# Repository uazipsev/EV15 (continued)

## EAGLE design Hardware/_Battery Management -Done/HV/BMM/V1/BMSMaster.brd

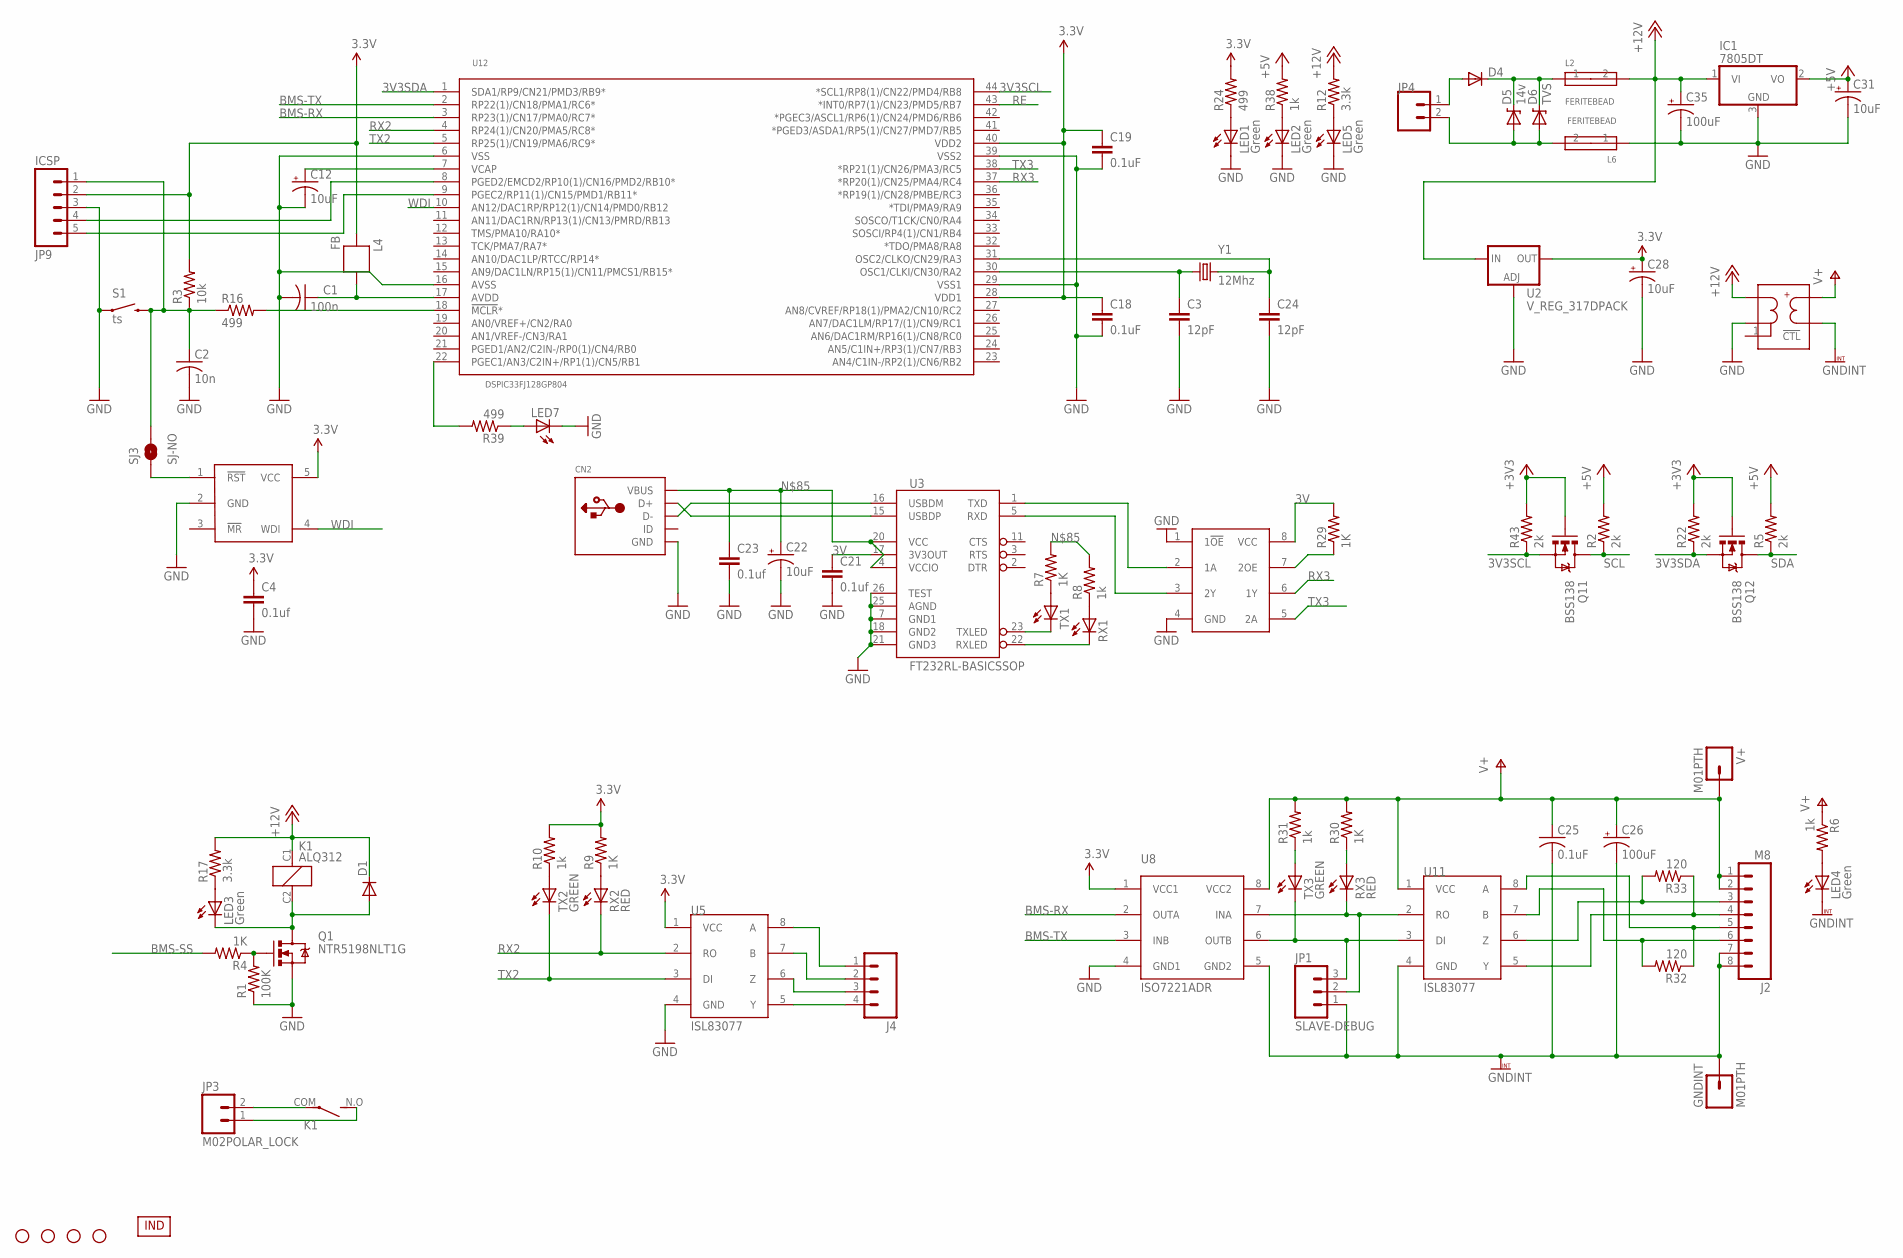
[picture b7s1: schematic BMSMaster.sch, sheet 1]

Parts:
C1: 100n; C0805
C2: 10n; C0805
C3, C24: 12pF; 0805
C4, C21, C23: 0.1uf; 0805
C12, C22, C31: 10uF; EIA3216
C18, C19: 0.1uF; 0805
C25: 0.1uF; C0805
C26: 100uF; C/6032-28W
C28: 10uF; POLC1206
C35: 100uF; CT7343
CN2: USBMOLEX; USB-MINIB-THM-MOLEX
D1: DIODESMB; SMB-DIODE
D4: DIODESMA; SMA-DIODE
D5: 14v; SMB-DIODE
D6: TVS; DO-214AC
GNDINT: M01PTH; 1X01
IC1: 7805DT; TO252
J2: M8; 75869-132LF
J4: M04POLAR_LOCK; MOLEX-1X4_LOCK
JP1: SLAVE-DEBUG; 1X03_LOCK_LONGPADS
JP3, JP4: M02POLAR_LOCK; MOLEX-1X2_LOCK
JP9: ICSP; 1X05_LOCK_LONGPADS
K1: ALQ312
L2, L6: FERITEBEAD; 0603
L4: FB; 0603
LED1, LED2, LED3, LED4, LED5: Green; CHIPLED_0805
LED7: LEDCHIP-LED0805; CHIP-LED0805
Q1: NTR5198NLT1G; SOT23
Q11, Q12: BSS138; SOT23-3
R1: 100K; R0805
R2, R5, R22, R43: 2k; R0805
R3: 10k; 0805
R4, R7, R9, R29, R30: 1K; R0805
R6, R8, R10, R31, R38: 1k; R0805
R12, R17: 3.3k; R0805
R16, R39: 499; 0805
R24: 499; R0805
R32, R33: 120; R0805
RX1: LEDCHIPLED_0805; CHIPLED_0805
RX2, RX3: RED; CHIPLED_0805
S1: ts; TACTILE-PTH-SIDEEZ
SJ3: SJ-NO; SJ_2S-NO
STANDOFF1, STANDOFF2, STANDOFF3, STANDOFF4: STAND-OFF
TX1: LEDCHIPLED_0805; CHIPLED_0805
TX2, TX3: GREEN; CHIPLED_0805
U2: V_REG_317DPACK; V-REG_DPACK
U3: FT232RL-BASICSSOP; SSOP28DB
U4: SN74LVC2G241DCTR; VFSOP-8
U5, U11: ISL83077; SO08
U8: ISO7221ADR; SOIC-8
U9: MAX823; SOT23-5L
U12: DSPIC33FJ128GP804; TQFP-44
U21: REC7.5-1205SRW/H2/A/M; 24DIPMOD-8LEAD
U$1: INDPK1; PICKIT-PIN-1
V+: M01PTH; 1X01
Y1: 12Mhz; CRYSTAL-SMD-5X3

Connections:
3.3V: C4.1, C18.1, C19.1, C28.1 (+), JP9.2, L4.2, R3.2, R9.2, R10.2, R24.2, U2.4 (OUT), U5.1 (VCC), U8.1 (VCC1), U9.5 (VCC), U12.28 (VDD1), U12.40 (VDD2)
3V: C21.1, R29.2, U3.17 (3V3OUT), U4.8 (VCC)
3V3SCL: Q11.2 (S), R43.1, U12.44 (*SCL1/RP8(1)/CN22/PMD4/RB8)
3V3SDA: Q12.2 (S), R22.1, U12.1 (SDA1/RP9/CN21/PMD3/RB9*)
+3V3: Q11.1 (G), Q12.1 (G), R22.2, R43.2
+5V: C31.A (+), IC1.2 (VO), R2.2, R5.2, R38.2; also elsewhere on the board
+12V: C35.+, D1.C, IC1.1 (VI), K1.C1 (+), L2.2, R12.2, R17.2, U2.3 (IN), U21.22 (VIN+), U21.23 (VIN+)
BMS-RX: U8.2 (OUTA), U12.3 (RP23(1)/CN17/PMA0/RC7*)
BMS-SS: R4.2
BMS-TX: U8.3 (INB), U12.2 (RP22(1)/CN18/PMA1/RC6*)
GND: C1.2, C2.2, C3.2, C4.2, C12.C (-), C18.2, C19.2, C21.2, C22.C (-), C23.2, C24.2, C28.2 (-), C31.C (-), C35.-, CN2.GND, IC1.3 (GND), JP9.3, L6.1, LED1.C, LED2.C, LED5.C, LED7.C, Q1.2 (S), R1.1, S1.1, U2.1 (ADJ), U3.7 (GND1), U3.18 (GND2), U3.21 (GND3), U3.25 (AGND), U3.26 (TEST), U4.1 (1!OE), U4.4 (GND), U5.4 (GND), U8.4 (GND1), U9.2 (GND), U12.6 (VSS), U12.16 (AVSS), U12.29 (VSS1), U12.39 (VSS2), U21.2 (VIN-), U21.3 (VIN-); also elsewhere on the board
GNDINT: C25.2, C26.-, GNDINT.1, J2.7, J2.8, JP1.1, LED4.C, U8.5 (GND2), U11.4 (GND), U21.16 (VOUT-)
unnamed: LED7.A, R39.1
unnamed: C24.1, U12.31 (OSC2/CLKO/CN29/RA3), Y1.3 (2)
unnamed: J4.4, U5.5 (Y)
unnamed: C3.1, U12.30 (OSC1/CLKI/CN30/RA2), Y1.1
unnamed: SJ3.1, U9.1 (!RST)
unnamed: CN2.D-, U3.16 (USBDM)
unnamed: LED1.A, R24.1
unnamed: CN2.D+, U3.15 (USBDP)
unnamed: LED5.A, R12.1
unnamed: R7.1, TX1.A
unnamed: J4.3, U5.6 (Z)
unnamed: J4.2, U5.7 (B)
unnamed: J4.1, U5.8 (A)
unnamed: R8.1, RX1.A
unnamed: TX1.C, U3.23 (TXLED)
unnamed: RX1.C, U3.22 (RXLED)
unnamed: R10.1, TX2.A
unnamed: U3.1 (TXD), U4.2 (1A)
unnamed: JP3.2, K1.COM
unnamed: U3.5 (RXD), U4.3 (2Y)
unnamed: C1.1, L4.1, U12.17 (AVDD)
unnamed: LED2.A, R38.1
unnamed: JP3.1, K1.N.O (S)
unnamed: J2.3, R33.2, U11.6 (Z)
unnamed: C12.A (+), U12.7 (VCAP)
unnamed: LED4.A, R6.2
unnamed: D1.A, K1.C2 (-), LED3.C, Q1.3 (D)
unnamed: Q1.1 (G), R1.2, R4.1
unnamed: R9.1, RX2.A
unnamed: J2.4, R33.1, U11.5 (Y)
unnamed: J2.5, R32.1, U11.8 (A)
unnamed: J2.6, R32.2, U11.7 (B)
unnamed: R39.2, U12.22 (PGEC1/AN3/C2IN+/RP1(1)/CN5/RB1)
unnamed: C2.1, JP9.1, R3.1, R16.1, S1.2, SJ3.2
unnamed: R16.2, U12.18 (!MCLR!*)
unnamed: JP9.4, U12.8 (PGED2/EMCD2/RP10(1)/CN16/PMD2/RB10*)
unnamed: JP9.5, U12.9 (PGEC2/RP11(1)/CN15/PMD1/RB11*)
unnamed: LED3.A, R17.1
unnamed: R29.1, U4.7 (2OE)
unnamed: R30.1, RX3.A
unnamed: R31.1, TX3.A
unnamed: C22.A (+), C23.1, CN2.VBUS, R7.2, R8.2, U3.4 (VCCIO), U3.20 (VCC)
unnamed: D5.A, D6.A, JP4.2, L6.2
unnamed: D4.A, JP4.1
unnamed: D4.C, D5.C, D6.C, L2.1
PIC1: JP1.2, RX3.C, U8.7 (INA), U11.2 (RO)
PIC2: JP1.3, TX3.C, U8.6 (OUTB), U11.3 (DI)
RE: U12.43 (*INT0/RP7(1)/CN23/PMD5/RB7)
RX2: RX2.C, U5.2 (RO), U12.4 (RP24(1)/CN20/PMA5/RC8*)
RX3: U4.6 (1Y), U12.37 (*RP20(1)/CN25/PMA4/RC4)
SCL: Q11.3 (D), R2.1; also elsewhere on the board
SDA: Q12.3 (D), R5.1; also elsewhere on the board
TX2: TX2.C, U5.3 (DI), U12.5 (RP25(1)/CN19/PMA6/RC9*)
TX3: U4.5 (2A), U12.38 (*RP21(1)/CN26/PMA3/RC5)
V+: C25.1, C26.+, J2.1, J2.2, R6.1, R30.2, R31.2, U8.8 (VCC2), U11.1 (VCC), U21.14 (VOUT+), V+.1
WDI: U9.4 (WDI), U12.10 (AN12/DAC1RP/RP12(1)/CN14/PMD0/RB12)

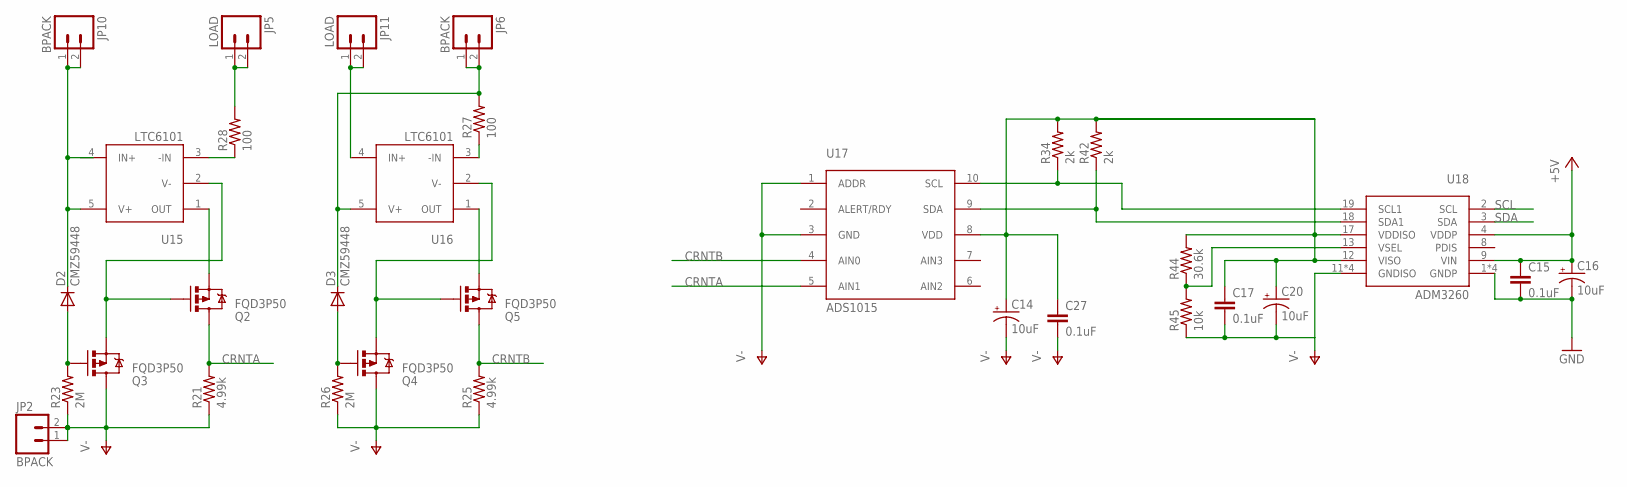
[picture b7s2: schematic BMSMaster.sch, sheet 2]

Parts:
C14, C16, C20: 10uF; EIA3216
C15, C17, C27: 0.1uF; 0805
D2, D3: CMZ59448; DIODE-HV
JP2, JP6, JP10: BPACK; MOLEX-1X2_LOCK
JP5, JP11: LOAD; MOLEX-1X2_LOCK
Q2, Q3, Q4, Q5: FQD3P50; DPAK
R21, R25: 4.99k; 1206
R23, R26: 2M; 1206
R27, R28: 100; 1206
R34, R42: 2k; 0805
R44: 30.6k; 0805
R45: 10k; 0805
U15, U16: LTC6101; SOT23-5
U17: ADS1015; MSOP-10
U18: ADM3260; SSOP-20

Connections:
+5V: C15.1, C16.A (+), U18.4 (VDDP), U18.9 (VIN); also elsewhere on the board
CRNTA: Q2.2 (D), R21.2, U17.5 (AIN1)
CRNTB: Q5.2 (D), R25.2, U17.4 (AIN0)
GND: C15.2, C16.C (-), U18.1 (GNDP), U18.5 (GNDP), U18.7 (GNDP), U18.10 (GNDP); also elsewhere on the board
unnamed: D3.C, JP6.1, JP6.2, R27.2, U16.5 (V+)
unnamed: JP5.1, JP5.2, R28.2
unnamed: D2.C, JP10.1, JP10.2, U15.4 (IN+), U15.5 (V+)
unnamed: D3.A, Q4.1 (G), R26.2
unnamed: C14.A (+), C17.1, C20.A (+), C27.1, R34.2, R42.2, R44.2, U17.8 (VDD), U18.12 (VISO), U18.17 (VDDISO)
unnamed: JP11.1, JP11.2, U16.4 (IN+)
unnamed: D2.A, Q3.1 (G), R23.2
unnamed: R34.1, U17.10 (SCL), U18.19 (SCL1)
unnamed: R27.1, U16.3 (-IN)
unnamed: Q2.1 (G), Q3.3 (S), U15.2 (V-)
unnamed: Q2.3 (S), U15.1 (OUT)
unnamed: Q5.3 (S), U16.1 (OUT)
unnamed: Q4.3 (S), Q5.1 (G), U16.2 (V-)
unnamed: R28.1, U15.3 (-IN)
unnamed: R42.1, U17.9 (SDA), U18.18 (SDA1)
unnamed: R44.1, R45.2, U18.13 (VSEL)
SCL: U18.2 (SCL); also elsewhere on the board
SDA: U18.3 (SDA); also elsewhere on the board
V-: C14.C (-), C17.2, C20.C (-), C27.2, JP2.1, JP2.2, Q3.2 (D), Q4.2 (D), R21.1, R23.1, R25.1, R26.1, R45.1, U17.1 (ADDR), U17.3 (GND), U18.11 (GNDISO), U18.14 (GNDISO), U18.16 (GNDISO), U18.20 (GNDISO)

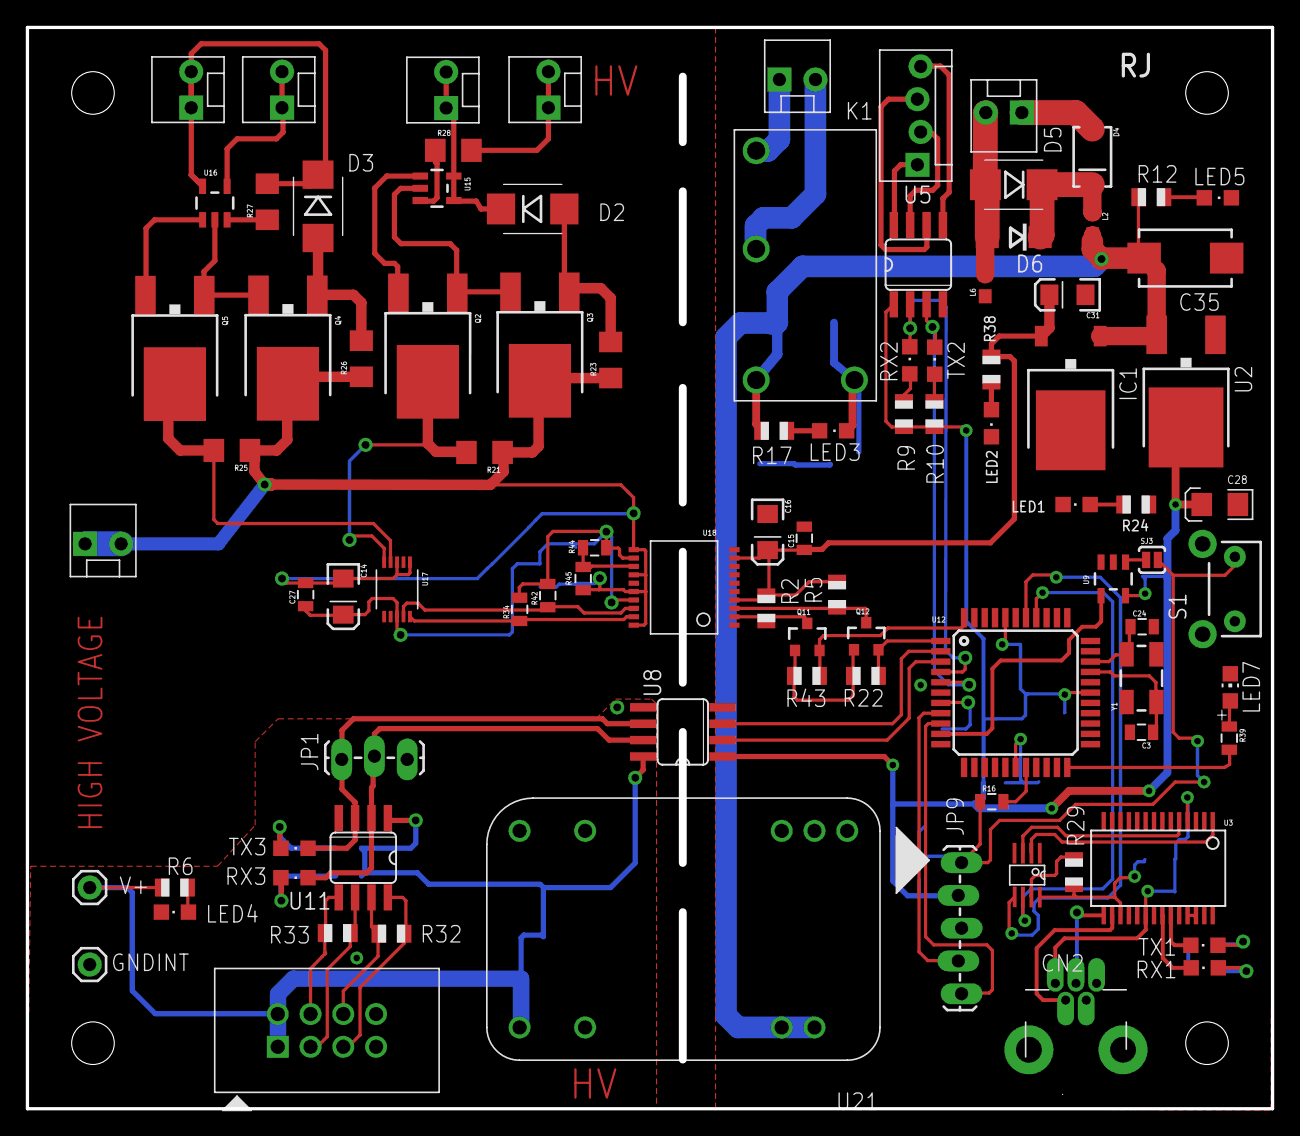
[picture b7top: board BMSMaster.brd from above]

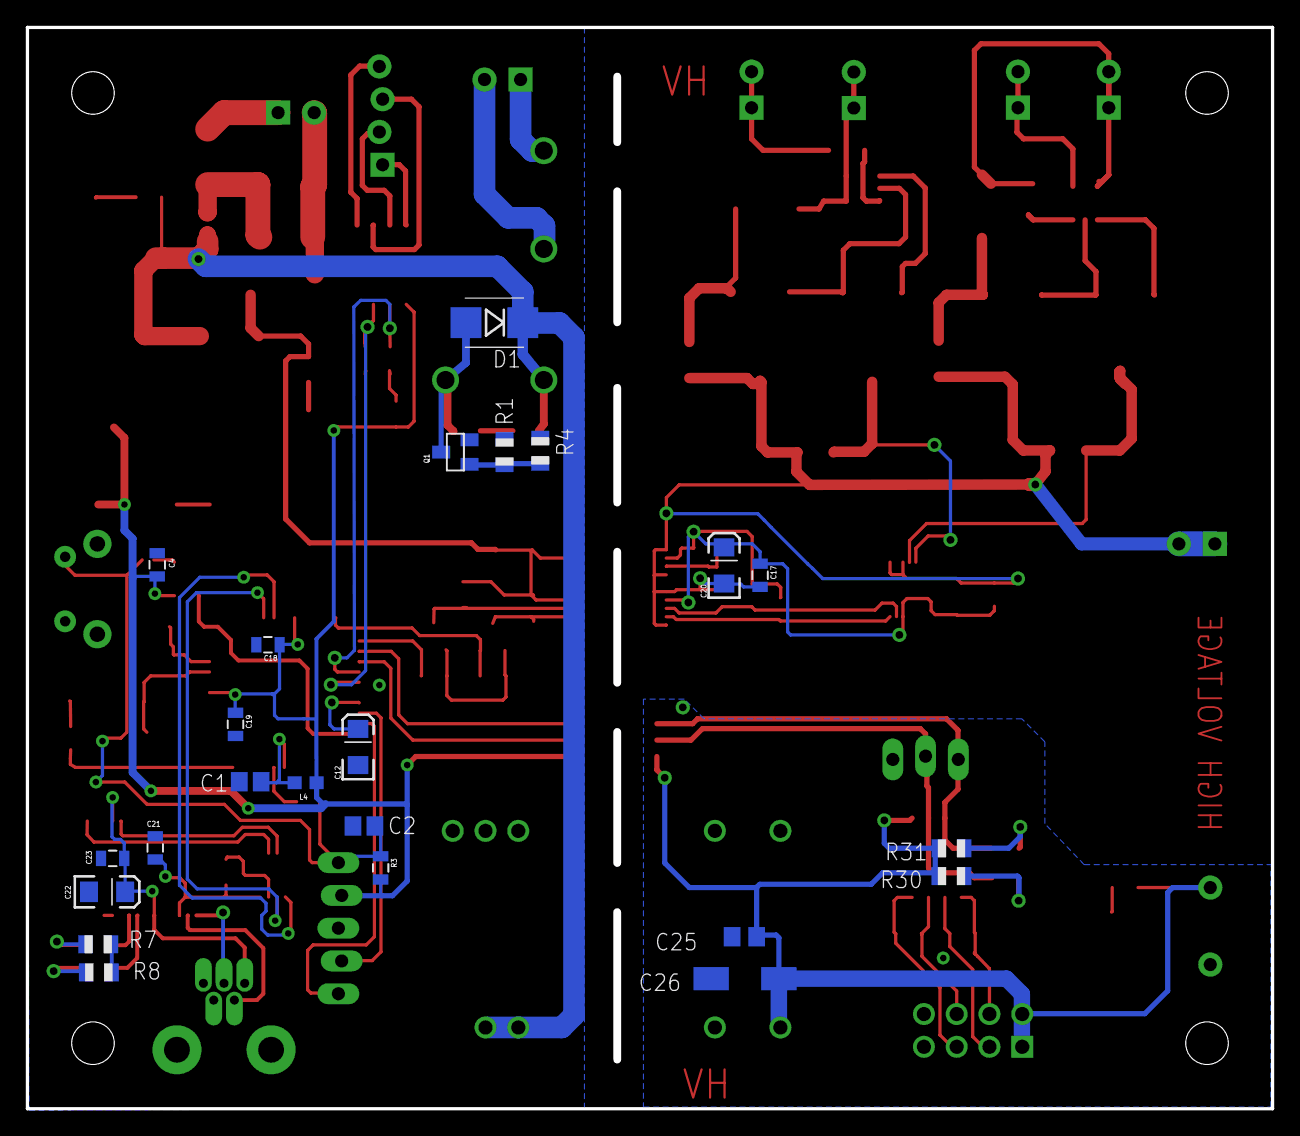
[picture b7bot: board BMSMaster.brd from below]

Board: 2 copper layers, 96.5 x 83.8 mm, 120 parts (23 on the bottom side), 85 nets.

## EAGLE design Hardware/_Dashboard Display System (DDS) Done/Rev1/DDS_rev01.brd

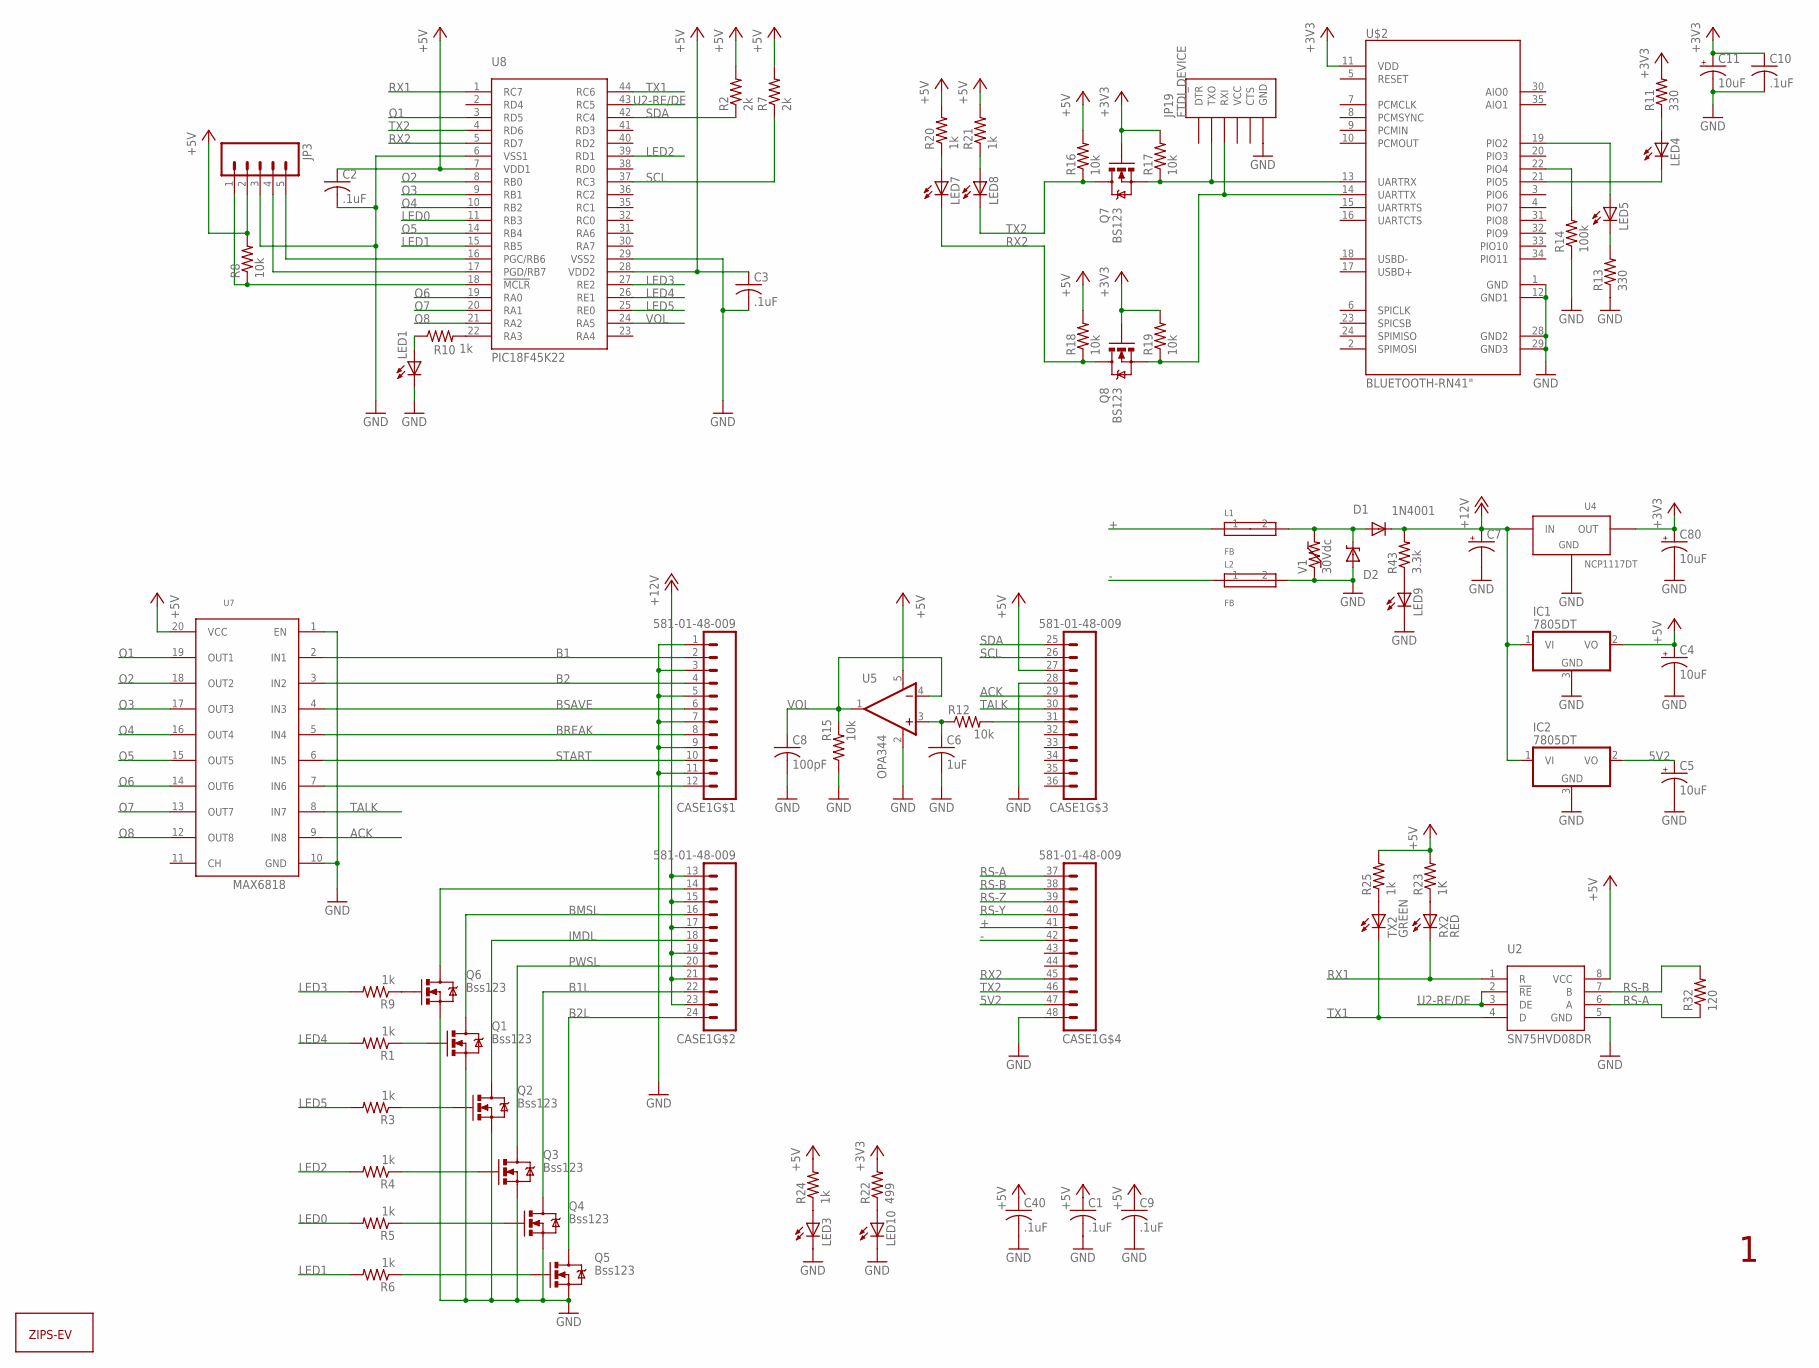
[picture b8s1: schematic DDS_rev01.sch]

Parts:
C1, C2, C3, C9, C10, C40: .1uF; C0805
C4, C5, C11, C80: 10uF; POLC1206
C6: 1uF; C0805
C7: CAP_POL7343; EIA7343
C8: 100pF; C0805
CASE1: 581-01-48-009
D1: 1N4001; SOD123
D2: MM5Z30; SOD-523F
IC1, IC2: 7805DT; TO252
JP3: M05LOCK_LONGPADS; 1X05_LOCK_LONGPADS
JP19: FTDI_DEVICE; FTDI_DEVICE_SIDE
L1, L2: FB; 0603
LED1, LED3, LED4, LED5, LED7, LED8, LED9, LED10: LEDCHIP-LED0805; CHIP-LED0805
Q1, Q2, Q3, Q4, Q5, Q6: Bss123; SOT23
Q7, Q8: BS123; SOT23
R1, R3, R4, R5, R6, R9, R10, R24, R25: 1k; R0805
R2, R7: 2k; R0805
R8, R16, R17, R18, R19: 10k; 0805
R11, R13: 330; 0805
R12, R15: 10k; R0805
R14: 100k; 0805
R20, R21: 1k; 0805
R22: 499; R0805
R23: 1K; R0805
R32: 120; R0805
R43: 3.3k; R0805
RX2: RED; CHIPLED_0805
TX2: GREEN; CHIPLED_0805
U2: SN75HVD08DR; SO-8
U4: NCP1117DT; DPAK
U5: OPA344; SOT23-5
U7: MAX6818; SSOP-20
U8: PIC18F45K22; TQFP-44
U$1: LOGO; L-L
U$2: BLUETOOTH-RN41"; RN41
V1: 30Vdc; 0603

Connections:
5V2: C5.1 (+), CASE1.47 (11), IC2.2 (VO)
+: CASE1.41 (5), L1.1
+3V3: C10.1, C11.1 (+), C80.1 (+), Q7.1 (G), Q8.1 (G), R11.2, R17.2, R19.2, R22.2, U4.2 (OUT), U$2.11 (VDD)
+5V: C1.1, C2.1, C3.1, C4.1 (+), C9.1, C40.1, CASE1.27 (3), IC1.2 (VO), JP3.2, R2.2, R7.2, R8.2, R16.2, R18.2, R20.2, R21.2, R23.2, R24.2, R25.2, U2.8 (VCC), U5.5 (V+), U7.20 (VCC), U8.7 (VDD1), U8.28 (VDD2)
+12V: C7.A (+), CASE1.13 (1), CASE1.15 (3), CASE1.17 (5), CASE1.19 (7), CASE1.21 (9), CASE1.23 (11), D1.C, IC1.1 (VI), IC2.1 (VI), R43.2, U4.3 (IN)
-: CASE1.42 (6), L2.1
ACK: CASE1.29 (5), U7.9 (IN8)
B1: CASE1.2, U7.2 (IN1)
B1L: CASE1.22 (10), Q4.3 (D)
B2: CASE1.4, U7.3 (IN2)
B2L: CASE1.24 (12), Q5.3 (D)
BMSL: CASE1.16 (4), Q1.3 (D)
BREAK: CASE1.8, U7.5 (IN4)
BSAVE: CASE1.6, U7.4 (IN3)
GHT: D1.A, D2.C, L1.2, V1.2
GND: C1.2, C2.2, C3.2, C4.2 (-), C5.2 (-), C6.2, C7.C (-), C8.2, C9.2, C10.2, C11.2 (-), C40.2, C80.2 (-), CASE1.1, CASE1.3, CASE1.5, CASE1.7, CASE1.9, CASE1.11, CASE1.28 (4), CASE1.48 (12), D2.A, IC1.3 (GND), IC2.3 (GND), JP3.3, JP19.P$6 (GND), L2.2, LED1.C, LED3.C, LED9.C, LED10.C, Q1.2 (S), Q2.2 (S), Q3.2 (S), Q4.2 (S), Q5.2 (S), Q6.2 (S), R13.1, R14.1, R15.1, U2.5 (GND), U4.1 (GND), U5.2 (V-), U7.1 (EN), U7.10 (GND), U8.6 (VSS1), U8.29 (VSS2), U$2.1 (GND), U$2.12 (GND1), U$2.28 (GND2), U$2.29 (GND3), V1.1
IMDL: CASE1.18 (6), Q2.3 (D)
LED0: R5.2, U8.11 (RB3)
LED1: R6.2, U8.15 (RB5)
LED2: R4.2, U8.39 (RD1)
LED3: R9.2, U8.27 (RE2)
LED4: R1.2, U8.26 (RE1)
LED5: R3.2, U8.25 (RE0)
unnamed: LED1.A, R10.1
unnamed: R10.2, U8.22 (RA3)
unnamed: JP19.P$3 (RXI), Q8.2 (S), R19.1, U$2.14 (UARTTX)
unnamed: CASE1.12, U7.7 (IN6)
unnamed: CASE1.14 (2), Q6.3 (D)
unnamed: LED4.A, R11.1
unnamed: Q6.1 (G), R9.1
unnamed: LED4.C, U$2.21 (PIO5)
unnamed: LED5.A, U$2.19 (PIO2)
unnamed: R14.2, U$2.22 (PIO4)
unnamed: JP19.P$2 (TXO), Q7.2 (S), R17.1, U$2.13 (UARTRX)
unnamed: LED5.C, R13.2
unnamed: LED9.A, R43.1
unnamed: Q1.1 (G), R1.1
unnamed: LED7.A, R20.1
unnamed: LED8.A, R21.1
unnamed: LED10.A, R22.1
unnamed: Q2.1 (G), R3.1
unnamed: Q3.1 (G), R4.1
unnamed: Q4.1 (G), R5.1
unnamed: Q5.1 (G), R6.1
unnamed: CASE1.31 (7), R12.2
unnamed: LED3.A, R24.1
unnamed: C6.1, R12.1, U5.3 (+IN)
unnamed: R25.1, TX2.A
unnamed: R23.1, RX2.A
unnamed: JP3.4, U8.17 (PGD/RB7)
unnamed: JP3.5, U8.16 (PGC/RB6)
unnamed: JP3.1, R8.1, U8.18 (!MCLR)
O1: U7.19 (OUT1), U8.3 (RD5)
O2: U7.18 (OUT2), U8.8 (RB0)
O3: U7.17 (OUT3), U8.9 (RB1)
O4: U7.16 (OUT4), U8.10 (RB2)
O5: U7.15 (OUT5), U8.14 (RB4)
O6: U7.14 (OUT6), U8.19 (RA0)
O7: U7.13 (OUT7), U8.20 (RA1)
O8: U7.12 (OUT8), U8.21 (RA2)
PWSL: CASE1.20 (8), Q3.3 (D)
RS-A: CASE1.37 (1), R32.1, U2.6 (A)
RS-B: CASE1.38 (2), R32.2, U2.7 (B)
RS-Y: CASE1.40 (4)
RS-Z: CASE1.39 (3)
RX1: RX2.C, U2.1 (R), U8.1 (RC7)
RX2: CASE1.45 (9), LED7.C, Q8.3 (D), R18.1, U8.5 (RD7)
SCL: CASE1.26 (2), R7.1, U8.37 (RC3)
SDA: CASE1.25 (1), R2.1, U8.42 (RC4)
START: CASE1.10, U7.6 (IN5)
TALK: CASE1.30 (6), U7.8 (IN7)
TX1: TX2.C, U2.4 (D), U8.44 (RC6)
TX2: CASE1.46 (10), LED8.C, Q7.3 (D), R16.1, U8.4 (RD6)
U2-RE/DE: U2.2 (!RE), U2.3 (DE), U8.43 (RC5)
VOL: C8.1, R15.2, U5.1 (OUT), U5.4 (-IN), U8.24 (RA5)

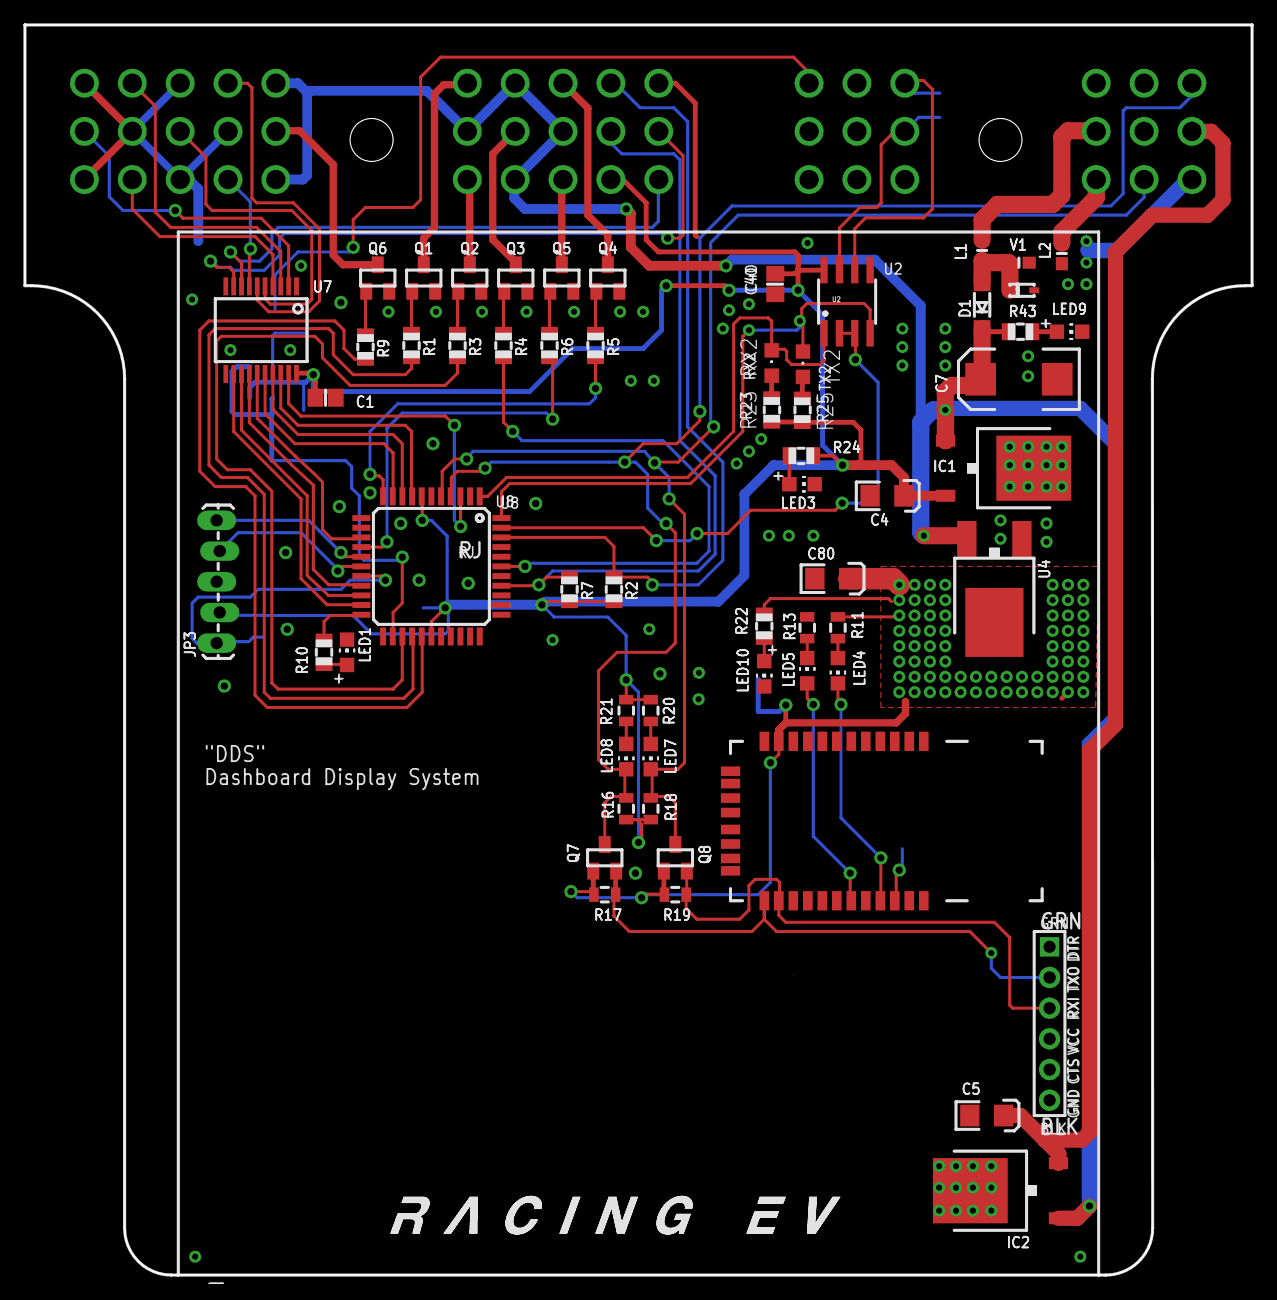
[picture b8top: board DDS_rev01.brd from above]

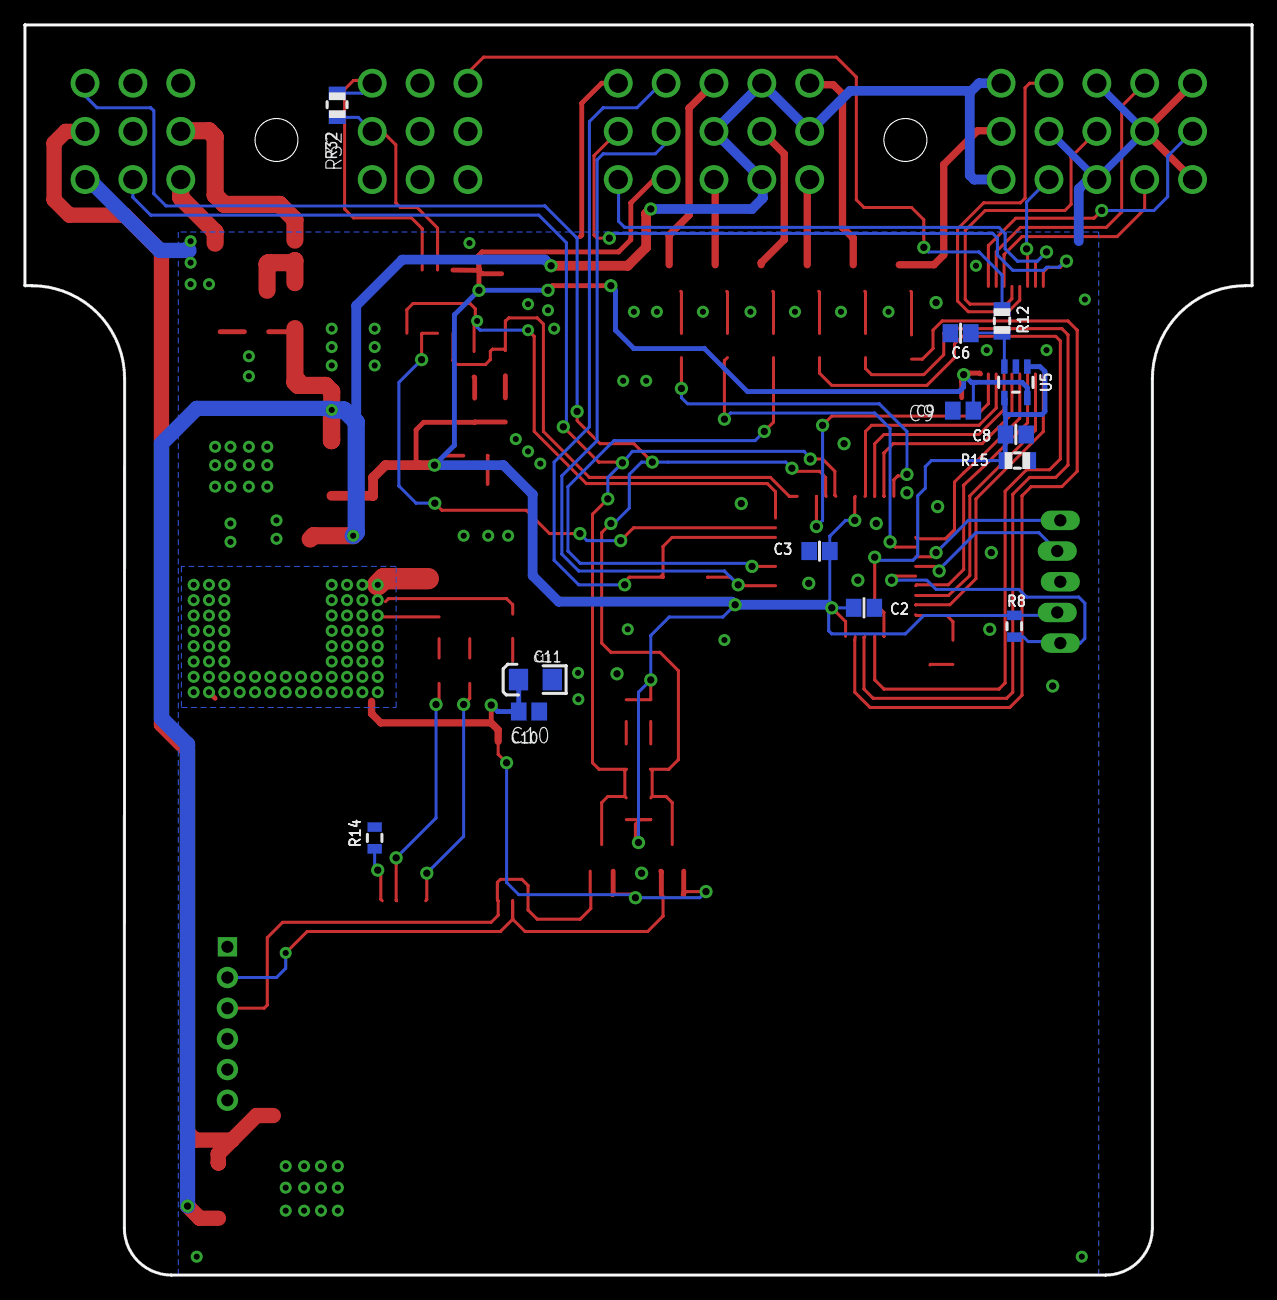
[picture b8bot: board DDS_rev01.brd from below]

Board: 2 copper layers, 101.6 x 103.5 mm, 75 parts (13 on the bottom side), 73 nets.

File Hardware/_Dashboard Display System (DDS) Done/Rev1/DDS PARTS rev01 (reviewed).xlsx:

| type | qty | Part | Value | Package
 | resistor | 1 | R32 | 120 | R0805
 | cap | 5 | C1, C2, C3, C9, C40 | .1uF | C0805
 | resistor | 1 | R14 | 100k | 805
 | cap | 1 | C8 | 100pF | C0805
 | resistor | 3 | R8, R12, R15 | 10k | 805
 | cap | 4 | C4, C5, C11, C80 | 10uF | POLC1206
 | resistor | 10 | R1, R3, R4, R5, R6, R9, R10, R23, R24, R25 | 1k | R0805
 | diode | 1 | D1 | 1N4001 | SOD123
 | cap | 1 | C6 | 1uF | C0805
 | resistor | 2 | R2, R7 | 2k | R0805
 | resistor | 1 | R43 | 3.3k | R0805
 |  | 1 | V1 | 30Vdc | 603
 | ic | 2 | IC1, IC2 | 7805DT | TO252
 | ic | 6 | Q1, Q2, Q3, Q4, Q5, Q6 | BS123 | SOT23
 | FB | 2 | L1, L2 | FB | 603
 | LED | 1 | TX2 | GREEN | CHIPLED_0805
 | ic | 1 | U7 | MAX6818 | SSOP-20
 | diode | 1 | D2 | MM5Z30 | SOD-523F
 | ic | 1 | U5 | OPA344 | SOT23-5
 | ic | 1 | U8 | PIC18F45K22 | TQFP-44
 | LED | 1 | RX2 | RED | CHIPLED_0805
 | ic | 1 | U2 | SN75HVD08DR | SO-8
 | cap | 1 | C7 |  | EIA7343
 | conn |  | JP3 |  | 1X05_LOCK_LONGPADS
 |  |  | LED1 |  | CHIP-LED0805 | Amber
 |  |  | LED3 |  | CHIP-LED0805 | Green
 |  |  | LED7 |  | CHIP-LED0805 | Red
 |  |  | LED8 |  | CHIP-LED0805 | Green
 |  |  | LED9 |  | CHIP-LED0805 | Green
Bluetooth Package | resistor | 2 | R11, R13 | 330 | 805
 | resistor | 1 | R22 | 499 | R0805
 | cap | 1 | C10 | .1uF | C0805
 | resistor | 1 | R14 | 100k | 805
 | resistor | 4 | R16, R17, R18, R19 | 10k | 805
 | cap | 1 | C11 | 10uF | POLC1206
 | resistor | 2 | R20, R21 | 1k | R0805
 | ic | 1 | U$2 | BLUETOOTH-RN41" | RN41
 | ic | 2 | Q7, Q8 | BS123 | SOT23
 | LED | 1 | TX2 | GREEN | CHIPLED_0805
 | ic | 1 | U4 | NCP1117DT | DPAK
 | LED | 1 | RX2 | RED | CHIPLED_0805
 |  |  | LED4 |  | CHIP-LED0805
 |  |  | LED5 |  | CHIP-LED0805
 |  |  | LED10 |  | CHIP-LED0805
 |  |  | JP19 | FTDI_DEVICE | FTDI_DEVICE_SIDE

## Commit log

2015-03-24 commit to include the development PCB files for reference as they are devved
2015-03-25 Fixed compile issue
2015-03-26 Fixed issues with ADC.c and added a few support functions.
2015-03-27 Added the exp filtering, ADC to voltage convert, adc to deg F, and indicator LED control.
2015-03-28 Reordered File structure
2015-03-30 added the Tmr 1 ADC starting on LV.
2015-04-04 Started on Bypass code.
2015-04-04 DDS button and LED code written
2015-04-13 cleanup
2015-04-13 Removed USB files
2015-04-14 added modbus / updated files
2015-04-30 added bypas code
2015-04-30 Have HV and LV BMS updated.
2015-05-02 updated HV and LV working
2015-05-03 made test fcn's and added doxy stuff
2015-05-06 Made changes to BMS-HV code...tested needs called
2015-05-11 Added PDU project and started Shift code
2015-05-11 Finished code and ready to test on BP
2015-05-11 fixed missing files
2015-05-11 Fixed up Shift code
2015-05-12 Added MCS and Have Digi-Pot almost done, started Motor Controller code
2015-05-13 Fixed upload
2015-05-15 update I2c
2015-05-17 Made many changes - started SAS code
2015-05-18 worked on shit
2015-05-19 DDS-I2C Bar working
2015-05-19 DDS board is done :)
2015-05-19 fixed file missing
2015-05-20 Weked on BMS-LV, mcs, SAS...
2015-05-20 MCS - I2C, motor control, and started on cooling stuff
2015-05-20 fixed data start error
2015-05-20 Worked on Motor Controller fcn's and SAS clock stuff.
2015-05-20 added missing files
2015-05-21 Made a lot of changes fan PWM running, cooling init code, clock code for a dsPics33Fj done. Dac code is working.
2015-05-26 BMM project added
2015-05-26 Cleaned up BMM and added required driver files.
2015-05-27 Added Horn fcn's to ECU and tested OK.
2015-05-27 Fixed PDU project corruption
2015-05-27 added commenting
2015-05-28 Getting the UARTs online
2015-05-28 Expanded for second UART, not going to implement the fasttransfer on this one yet.. able to switch between UART1 and UART if necessary for ECU bus
2015-05-28 Oh dear
2015-05-28 MCS stuff
2015-05-28 Added PDU fcn's
2015-05-28 Working SAS communications call/response
2015-05-28 PDU - update
2015-05-28 ECU updates
2015-05-28 PDU code updated and worked on ECU horn....fucked up horn code more
2015-05-29 Worked on PDU code.
2015-05-29 Removed old PDU zip file, added timer and memory code
2015-05-29 UART Communications Rev1
2015-05-30 fixed clock issue on BMM and upload issue
2015-05-31 updated PDU files
2015-05-31 added comments
2015-05-31 Cleaned and finished comments for BMS-HV
2015-05-31 Added comments And fixed PDU code issue
2015-05-31 Making comms magic happen
2015-05-31 Minor formatting changes
2015-06-01 8-bit comms untested
2015-06-01 Fixed broken code on Temp read Tested Bypass and voltage read.
2015-06-01 Fixed ADC ISR bug
2015-06-02 SAS comm direction issue fixed, PDU update, Need to implement fault correction.
2015-06-02 Comms Wrap Up
2015-06-03 MCS comms weird, BMM comms present (not implemented)
2015-06-03 Adding files to commit
2015-06-03 ADC work
2015-06-04 BMM work to make better functionality
2015-06-04 After banging head against wall for solid hour and a half, found bug, ADC1 Interrupt in SAS, when populated with code (mind you, this interrupt would never get called) the processor crashes in weird 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
2015-06-05 Migrated DDS-TEST.X to DDS.X
2015-06-05 made a bunch of fixes and updates
2015-06-06 Communications MCS started.. need to finalize
2015-06-07 BMS stuff
2015-06-07 ADC Functional to DDS
2015-06-07 Communications play.. seeking out a communications issue
2015-06-07 BMS_LV Comm issue SAS got a work-over, timer module is running very awkwardly
2015-06-07 Front end analog
2015-06-08 Lots of clean up, MCS comms installed, ECU throttle and brake checks and MCS DAC
2015-06-08 Auto formatting all around
2015-06-08 Something on the side I have been wanting to do.. Serial communication on a computer to our system.. need to implement the select comm port stuff for easy portability across computers
2015-06-09 ECU organization
2015-06-09 BMS Testing Updates
2015-06-09 Debug Manager Installed
2015-06-10 MCS Comms check integrated into boot sequence, stateMachine for BMM comms requests. Fault checking integrated. More to come
2015-06-10 Oooooo the updates... lots of goodies here.. power state control, mcs boots on ecu boot car, ecu waits for mcs comms
2015-06-10 DDS interface changed to report which button, ADDRESSING.h updates, State machine begins separation, PDU POWER_RAILS installed, MCS boot at ECU boot car sequence.. something special in there too... l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
2015-06-10 Forgot some files, again.. like a dumbass
2015-06-11 Battery management massive additions... BMS to BMM to ECU train established...
2015-06-11 Well I guess the BMM code is boned right now.. probably a matter of timing... adding another timer crashed it i think... nesting of interrupt changes the situation, for the better and the worse
2015-06-12 Fixes for BMM and BMS comms and reporting on ECU of all battery information, can also send a packet to instruct the ECU to debug different information
2015-06-12 Still having some issues with the BMM bootup, also a non functional transceiver on the BMM to M->S full duplex
2015-06-14 Stability BMM, comms from slave. stability SAS, slave code functionality for ADC
2015-06-14 I2C BMM installed and debugging
2015-06-14 Fully Functional?
2015-06-14 Including the charger code with this commit.. changes to BMS slave reading voltages
2015-06-15 Minor Changes
2015-06-16 have correct code for charger
2015-06-22 Final commit
2015-06-27 Added hardware files
2015-08-14 TM - adding telem code
2015-08-14 TSS - Init commit
2015-08-15 GPS stuff
2015-08-25 Updated code. Fixed control system issues. Added power save Code -UNTESTED
2015-09-15 Added PDU code and fixed shift registrar.
2015-09-15 Commenting on MCS communications and control code
2015-09-15 Remove 12 V manipulation to motor controller
2015-09-20 Added changes to the project.
2015-09-23 MCS work, ECU for MCS Compatibility, Check the timing changes, they were rough and may have caused issues... Stripped most of MCS functionality for debugging, still have issues with DAC freezing, uns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
2015-09-23 Cleaning up a little
2015-09-23 updated BMS-HV code
2015-09-24 fixed bug in MCS Communications.c
2015-10-09 Updates for slave comms on BMM and slave addressing
2015-10-11 I broke MCS needs fixed.
2015-10-15 BMM attempts, seems to be an issue with receiving data from the Slave comms. We physically see packets at the mux, so I am guessing it should be receiving code.. Maybe or maybe not, data is getting E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
2015-10-15 Broke the horn...
2015-10-17 added Charger control code.
2015-10-19 Cleaned up branch
2015-10-19 Started to clean up the UART stuff. Does not compile.
2015-11-18 Changed SetLEDOut() function to return a int that will have the value of the state given the led number and that state of the led is currently in. This is done through a Enum.
    -Andrew Thornborough
2015-11-24 1. Remade the SetLEDOut() function to change the LED lights as the function did before, but also added a state (state=2) for blinking the LED. I then made a array to the SetLEDOut() function to recor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
    2. I added a GetStateLED function which ask for a led number as a argument and returns that LED's state.
    3. I added a second SetLEDOut function but with different arguments, the idea here is that we can have one function which can set the led's to there state and have a fixed blink rate. While the other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
2015-12-02 Fixed DDS
2015-12-08 Added blink functionality for led's with timer2. Not sure if it will work there is a issue with my mplab giving errors that should not be. I will fix the IDE and then clean up code later.
    -Andrew Thornborough
2016-01-03 Corrected the Blink LED feature should be working now with no errors.
    Added function to change blink rate of led in the IO file.
    -Andrew Thornborough 1/2/2016
2016-01-03 Re did some code so some of the files stay consistent. The other commit I think had a lot of other stuff that was not necessary Official Update for blink LED.
    -Andrew Thornborough
2016-01-11 Working on UART cleanup.
2016-03-21 Some work to figure out the I2C files...
2016-04-03 BMS-BMM update
2016-08-17 2015 code from dropbox.
